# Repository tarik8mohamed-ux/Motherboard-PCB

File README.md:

# Hyperloop Motherboard PCB
Hyperloop Motherboard PCB Design (KiCad Schematics, component footprints, layouts, and diagrams)

Cornell Hyperloop SP'26
ECC:   Tarik, Peri, Farah, and Vinny

## Introduction: 
This project is a central control PCB designed to serve as the primary communication and motor control hub for Cornell Hyperloop's MiniPod. The board integrates multiple communication protocols to interface with a variety of peripherals: CANopen for servo motor control via the EPOS2 70/10, Step/Dir for stepper motor control via the TB6600, I2C for a distributed sensor network of temperature and current monitors, and PWM for fan speed control. The modular architecture supports hot-pluggable expansion, allowing sensors, MCU, and Multiplexers to be swapped or added without disrupting system operation. The board is ~265mm x 135mm and consists of 4 Layers: Signal-GND-PWR-Signal, with the PWR plane seperated into 3.3V,5.0V, and 12V sections to support different components. The most up to date files are in the Hyperloop Organized PCB folder.

## Components:
Cornell Hyperloop's MiniPod is ~7ft, meaning that sesnors and motors must be controlled by the motherbaord from a distance. This is why most components will be connected to the PCB via Cable/Wire connectors.
#### MCU:
The motherboard is controlled with an Arduino Nano R4
<table>
  <tr>
    <td align="center"><b>Arduino Nano R4</b></td>
  </tr>
  <tr>
    <td></td>
  </tr>
</table>

#### Sensors & Fan Control:
Overheating and current spikes are critical concerns on the Pod, so temperature and current sensors are distributed throughout. Temperature sensors use 8-pin Molex connectors (2 power, 2 communication, 1 interrupt, 3 alert pins), while current sensors use 4-pin Molex connectors (2 power, 2 communication pins). Vin+ and Vin− are connected across the points being measured, not the board, and I²C addresses are permanently hardset on the board. Additionally, a TCA9548A I2C multiplexer was integrated to expand the single I2C bus into up to 8 independent channels. 4-pin cooling fans are also distributed across the Pod, represented as 4-pin Molex connectors.
<table>
  <tr>
    <td align="center"><b>Temperature Sensor: MCP9808 </b></td>
    <td align="center"><b>Current Sensor: INA260</b></td>
    <td align="center"><b>Fan: Arctic P12</b></td>
    <td align="center"><b>Multiplexer: TCA9548A</b></td>
  </tr>
  <tr>
    <td></td>
    <td></td>
    <td></td>
    <td></td>
  </tr>
</table>

#### Motor Control:
The Pod interfaces with a TB6600 stepper driver and an EPOS2 70/10 servo controller. The TB6600 is controlled via Step/Dir/Enable signals through a Phoenix Contact screw terminal, and the EPOS2 communicates over CANopen through a Molex Micro-Fit 3.0 4-pin connector.
<table>
  <tr>
    <td align="center"><b>4-pin Pheonix Contact Screw Terminal</b></td>
    <td align="center"><b>Molex Micro-Fir 3.0 4-pin connector</b></td>
  </tr>
  <tr>
    <td></td>
    <td></td>
  </tr>
</table>

#### GPIO Expander:
An MCP23017 I2C expander is included to provide additional GPIO pins for the Pod as needed. Breakout headers expose all 16 I/O pins for flexible peripheral connections.
The motherboard is controlled with an Arduino Nano R4
<table>
  <tr>
    <td align="center"><b>MCP23017 I2C Expander:</b></td>
  </tr>
  <tr>
    <td></td>
  </tr>
</table>

#### Power, Resistors, Capacitors:
The PCB contains 3.3V,5.0V, and 12.0V sections in the power plane. XT30 connectors will be used to connect external battery packs to drive the power plane.
Resistors typically take on the role of pull-ups in this design. Through-Hole Resistors are used for ease of soldering. On the other hand, capacitors are typically used for bypass or decoupling. In this context, we picked SMD capacitors despite the extra difficulty in soldering because they significantly outperform THT.
<table>
  <tr>
    <td align="center"><b>XT30 Connector:</b></td>
  </tr>
  <tr>
    <td></td>
  </tr>
</table>

## Communication Systems:
### I2C Sensor Network & I2C Expander:
The I2C network, located in the top left of the PCB, is managed by a TCA9548A multiplexer which expands the microcontroller's single I2C bus into 4 independent channels, each with its own pull-up resistors to maintain signal integrity. Each channel hosts sensor peripherals, with every device supported by a dedicated decoupling capacitor for noise suppression. A series resistor on the main I2C line dampens inductive ringing before the signal reaches the multiplexer. MCP9808 temperature sensors feature an active-low alert pin connected to a microcontroller GPIO, enabling interrupt-driven temperature monitoring without continuous polling. An MCP23017 I2C I/O expander is also connected to the bus, currently populated with breakout headers for flexible future peripheral connections.

### CAN EPOS2 70/10:
CANopen communication is implemented using a TCAN332 transceiver, which converts the microcontroller's TX/RX signals into differential CANH/CANL signals. A 120Ω termination resistor is placed at the output connector to prevent signal reflections. The bus connects to an EPOS2 70/10 servo controller via a Molex Micro-Fit 3.0 cable. It is located below the MCU.

### Step/Dir TB6600:
The TB6600 stepper driver is controlled via three GPIO signals — PUL+, DIR+, and ENA+ — using a common-cathode wiring configuration. Series resistors on each line dampen signal ringing before reaching the Phoenix Contact screw terminal output connector. It is located just above the MCU.

### PWM Fan CTRL:
Two pairs of fans are controlled via PWM signals from the microcontroller, with each pair sharing a single PWM output to conserve GPIO pins. One tachometer signal per pair is routed back to a microcontroller GPIO, providing RPM feedback for monitoring fan speed. Each fan connector includes dedicated power and ground connections for reliable operation. It is located on the right side of the board.

## Future Updates
-INA260 Alert Pin: The INA260 current sensor connector will be expanded from 4 to 5 pins to expose the ALERT pin, enabling interrupt-driven current monitoring in place of polling across the I2C channels and significantly improving CPU efficiency.    

-TCAN332 Connector Orientation: The CAN connector will be changed from horizontal to vertical to improve accessibility and PCB layout clarity.

-Component Density: Component placement will be optimized for a smaller board footprint, reducing fabrication cost.

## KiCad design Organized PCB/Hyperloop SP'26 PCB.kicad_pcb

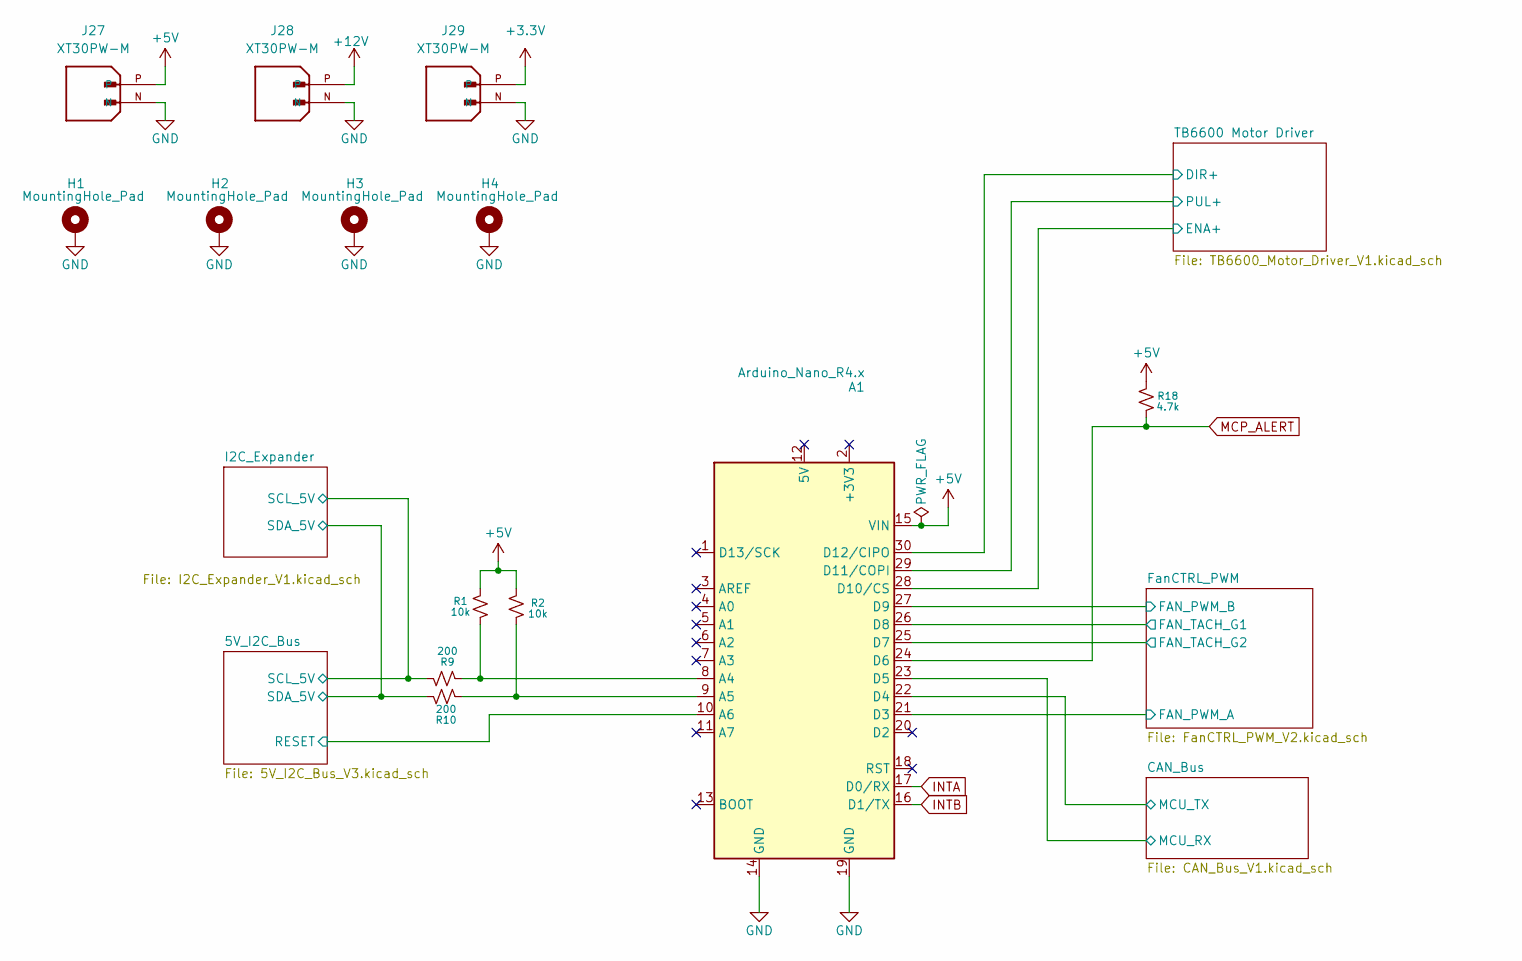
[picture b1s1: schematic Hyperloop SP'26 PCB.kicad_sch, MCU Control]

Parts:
A1: Arduino_Nano_R4.x; Arduino_Nano
H1, H2, H3, H4: MountingHole_Pad; MountingHole_3.2mm_M3_Pad_TopBottom
J27, J28, J29: XT30PW-M; AMASS_XT30PW-M; PARTREV 1.2
R1, R2: 10k; R_Axial_DIN0207_L6.3mm_D2.5mm_P7.62mm_Horizontal
R9, R10: 200; R_Axial_DIN0207_L6.3mm_D2.5mm_P7.62mm_Horizontal
R18: 4.7k; R_Axial_DIN0207_L6.3mm_D2.5mm_P7.62mm_Horizontal

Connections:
+3.3V: J29.P; also elsewhere on the board
+5V: A1.15 (VIN), J27.P, R1.2, R2.2, R18.2; also elsewhere on the board
+12V: J28.P; also elsewhere on the board
/5V_I2C_Bus/RESET: A1.10 (A6); also elsewhere on the board
/5V_I2C_Bus/SCL_5V: R9.2; also elsewhere on the board
/5V_I2C_Bus/SDA_5V: R10.2; also elsewhere on the board
/CAN_Bus/MCU_RX: A1.23 (D5); also elsewhere on the board
/CAN_Bus/MCU_TX: A1.22 (D4); also elsewhere on the board
/FanCTRL_PWM/FAN_PWM_A: A1.21 (D3); also elsewhere on the board
/FanCTRL_PWM/FAN_PWM_B: A1.27 (D9); also elsewhere on the board
/FanCTRL_PWM/FAN_TACH_G1: A1.26 (D8); also elsewhere on the board
/FanCTRL_PWM/FAN_TACH_G2: A1.25 (D7); also elsewhere on the board
/TB6600 Motor Driver/DIR+: A1.30 (D12/CIPO); also elsewhere on the board
/TB6600 Motor Driver/ENA+: A1.28 (D10/CS); also elsewhere on the board
/TB6600 Motor Driver/PUL+: A1.29 (D11/COPI); also elsewhere on the board
GND: A1.14 (GND), A1.19 (GND), H1.1, H2.1, H3.1, H4.1, J27.N, J28.N, J29.N; also elsewhere on the board
INTA: A1.17 (D0/RX); also elsewhere on the board
INTB: A1.16 (D1/TX); also elsewhere on the board
MCP_ALERT: A1.24 (D6), R18.1; also elsewhere on the board
unnamed: A1.8 (A4), R1.1, R9.1
unnamed: A1.9 (A5), R2.1, R10.1

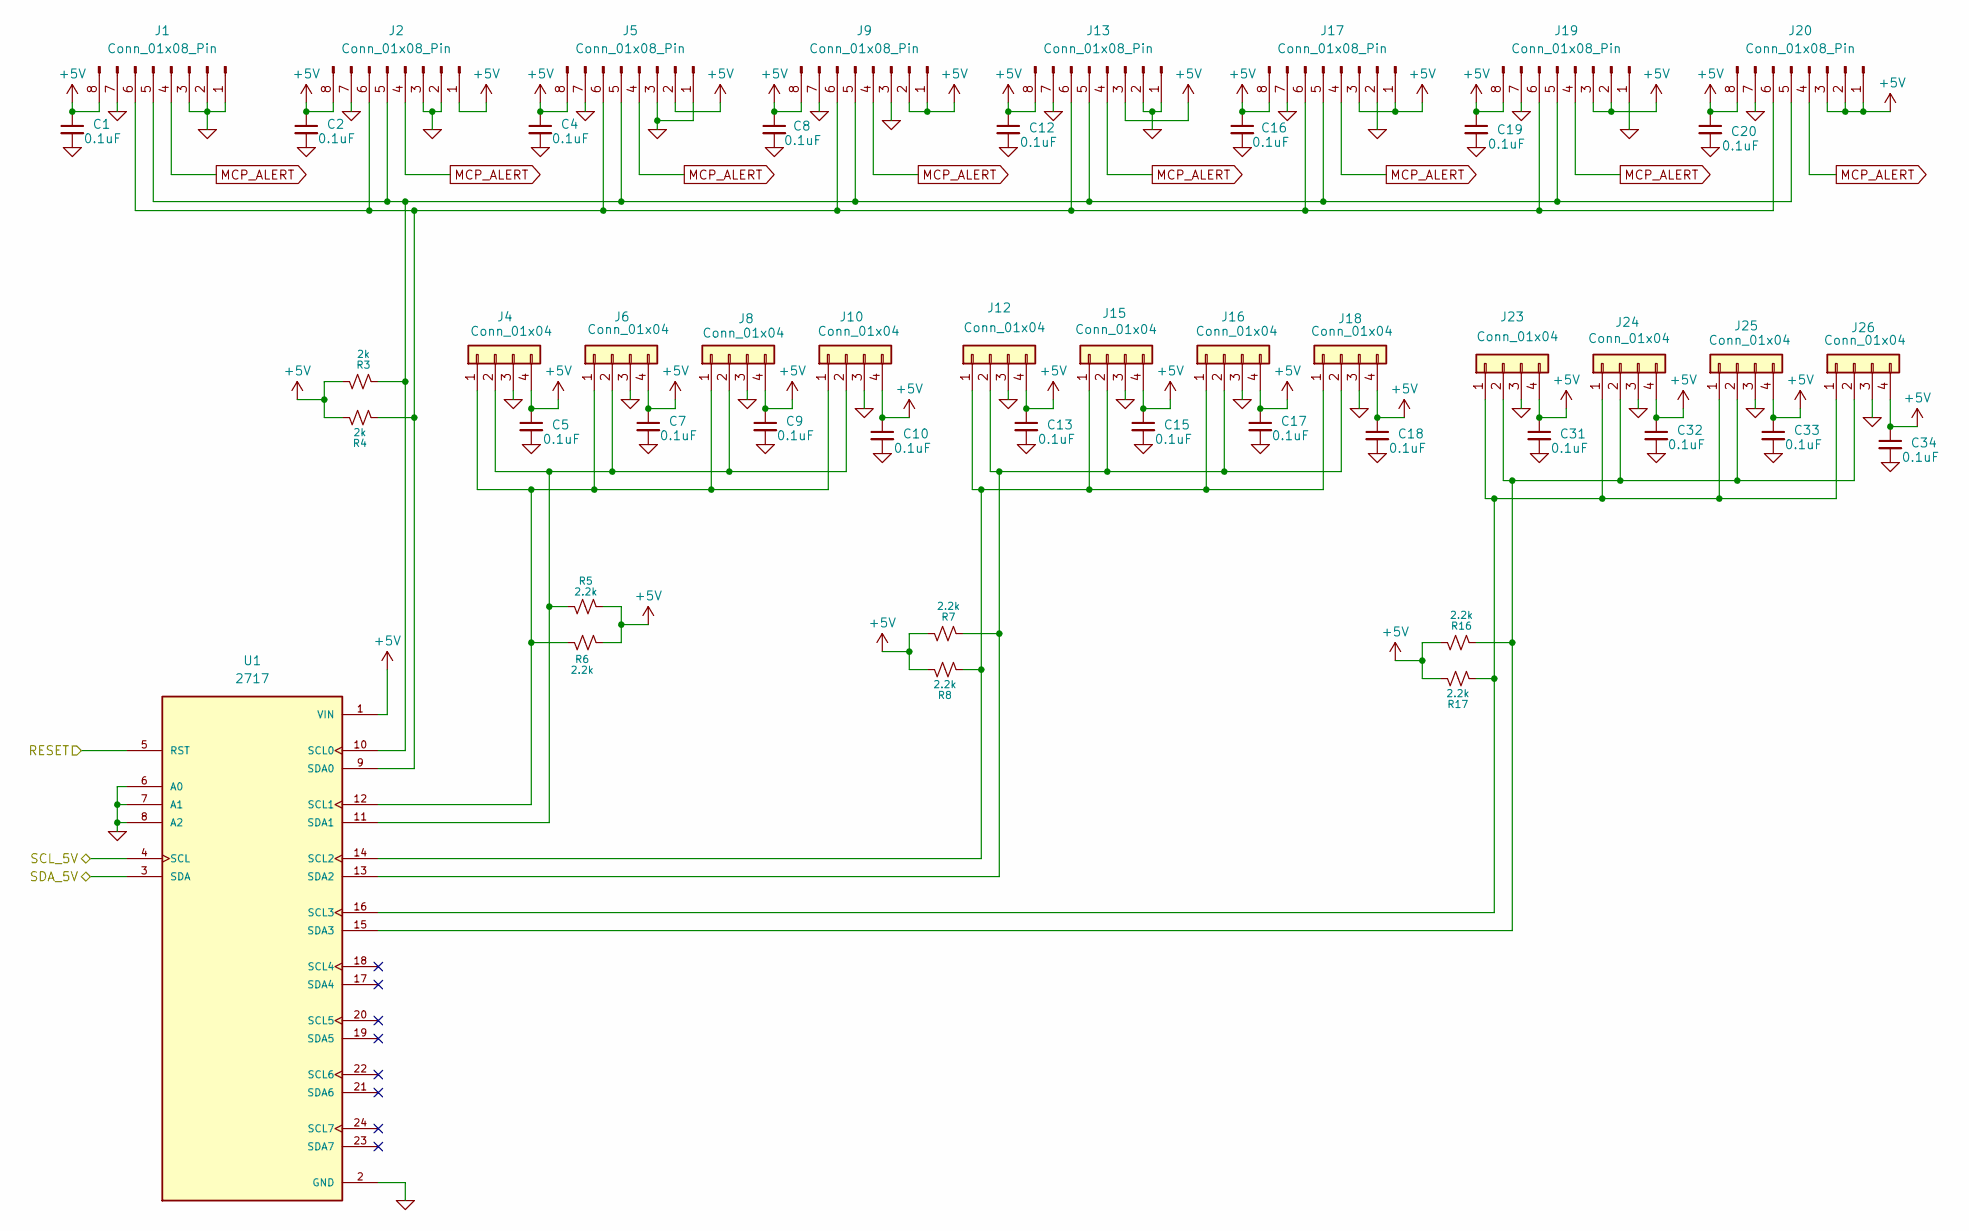
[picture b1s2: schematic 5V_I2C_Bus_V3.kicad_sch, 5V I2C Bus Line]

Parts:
C1, C2, C4, C5, C7, C8, C9, C10, C12, C13, C15, C16, C17, C18, C19, C20, C31, C32, C33, C34: 0.1uF; C_0805_2012Metric
J1, J2, J5, J9, J13, J17, J19, J20: Conn_01x08_Pin; Molex_KK-254_AE-6410-08A_1x08_P2.54mm_Vertical
J4, J6, J8, J10, J12, J15, J16, J18, J23, J24, J25, J26: Conn_01x04; Molex_KK-254_AE-6410-04A_1x04_P2.54mm_Vertical
R3, R4: 2k; R_Axial_DIN0207_L6.3mm_D2.5mm_P7.62mm_Horizontal
R5, R6, R7, R8, R16, R17: 2.2k; R_Axial_DIN0207_L6.3mm_D2.5mm_P7.62mm_Horizontal
U1: 2717; MODULE_2717; PARTREV Sep 11, 2015

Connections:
+5V: C1.1, C2.1, C4.1, C5.1, C7.1, C8.1, C9.1, C10.1, C12.1, C13.1, C15.1, C16.1, C17.1, C18.1, C19.1, C20.1, C31.1, C32.1, C33.1, C34.1, J1.8, J2.1, J2.8, J4.4, J5.2, J5.8, J6.4, J8.4, J9.1, J9.2, J9.8, J10.4, J12.4, J13.3, J13.8, J15.4, J16.4, J17.1, J17.3, J17.8, J18.4, J19.2, J19.3, J19.8, J20.1, J20.2, J20.3, J20.8, J23.4, J24.4, J25.4, J26.4, R3.2, R4.2, R5.2, R6.2, R7.2, R8.2, R16.2, R17.2, U1.1 (VIN); also elsewhere on the board
/5V_I2C_Bus/RESET: U1.5 (RST); also elsewhere on the board
/5V_I2C_Bus/SCL_5V: U1.4 (SCL); also elsewhere on the board
/5V_I2C_Bus/SDA_5V: U1.3 (SDA); also elsewhere on the board
GND: C1.2, C2.2, C4.2, C5.2, C7.2, C8.2, C9.2, C10.2, C12.2, C13.2, C15.2, C16.2, C17.2, C18.2, C19.2, C20.2, C31.2, C32.2, C33.2, C34.2, J1.1, J1.2, J1.3, J1.7, J2.2, J2.3, J2.7, J4.3, J5.1, J5.3, J5.7, J6.3, J8.3, J9.3, J9.7, J10.3, J12.3, J13.1, J13.2, J13.7, J15.3, J16.3, J17.2, J17.7, J18.3, J19.1, J19.7, J20.7, J23.3, J24.3, J25.3, J26.3, U1.2 (GND), U1.6 (A0), U1.7 (A1), U1.8 (A2); also elsewhere on the board
MCP_ALERT: J1.4, J2.4, J5.4, J9.4, J13.4, J17.4, J19.4, J20.4; also elsewhere on the board
unnamed: J1.5, J2.5, J5.5, J9.5, J13.5, J17.5, J19.5, J20.5, R3.1, U1.10 (SCL0)
unnamed: J1.6, J2.6, J5.6, J9.6, J13.6, J17.6, J19.6, J20.6, R4.1, U1.9 (SDA0)
unnamed: J4.1, J6.1, J8.1, J10.1, R6.1, U1.12 (SCL1)
unnamed: J4.2, J6.2, J8.2, J10.2, R5.1, U1.11 (SDA1)
unnamed: J12.1, J15.1, J16.1, J18.1, R8.1, U1.14 (SCL2)
unnamed: J12.2, J15.2, J16.2, J18.2, R7.1, U1.13 (SDA2)
unnamed: J23.1, J24.1, J25.1, J26.1, R17.1, U1.16 (SCL3)
unnamed: J23.2, J24.2, J25.2, J26.2, R16.1, U1.15 (SDA3)

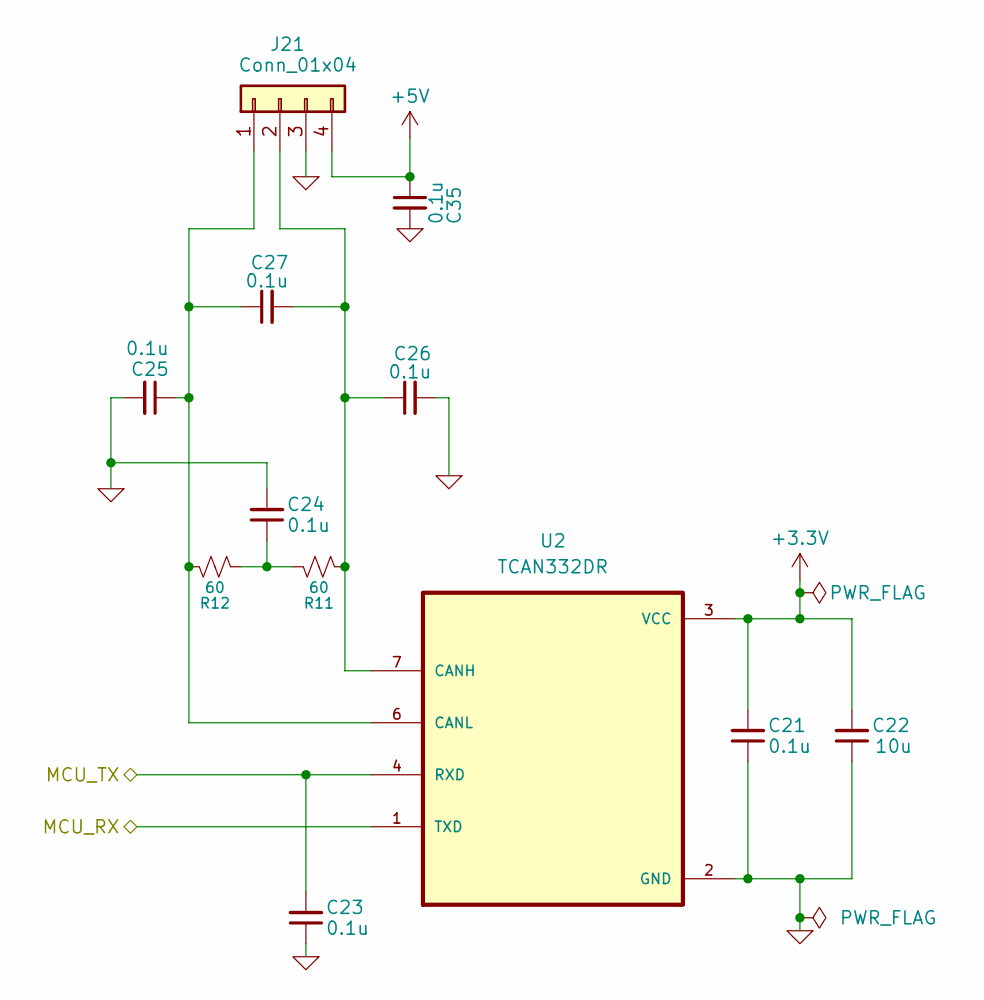
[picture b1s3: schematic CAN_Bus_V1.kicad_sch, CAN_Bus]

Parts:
C21, C23, C24, C25, C26, C27, C35: 0.1u; C_0805_2012Metric
C22: 10u; C_0805_2012Metric
J21: Conn_01x04; Molex_Micro-Fit_3.0_43045-0400_2x02_P3.00mm_Horizontal
R11, R12: 60; R_Axial_DIN0207_L6.3mm_D2.5mm_P7.62mm_Horizontal
U2: TCAN332DR; SOIC127P599X175-8N(TCAN332DR)

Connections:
+3.3V: C21.2, C22.2, U2.3 (VCC); also elsewhere on the board
+5V: C35.1, J21.4; also elsewhere on the board
/CAN_Bus/MCU_RX: U2.1 (TXD); also elsewhere on the board
/CAN_Bus/MCU_TX: C23.2, U2.4 (RXD); also elsewhere on the board
GND: C21.1, C22.1, C23.1, C24.2, C25.2, C26.2, C35.2, J21.3, U2.2 (GND); also elsewhere on the board
unnamed: C24.1, R11.2, R12.1
unnamed: C25.1, C27.1, J21.1, R12.2, U2.6 (CANL)
unnamed: C26.1, C27.2, J21.2, R11.1, U2.7 (CANH)

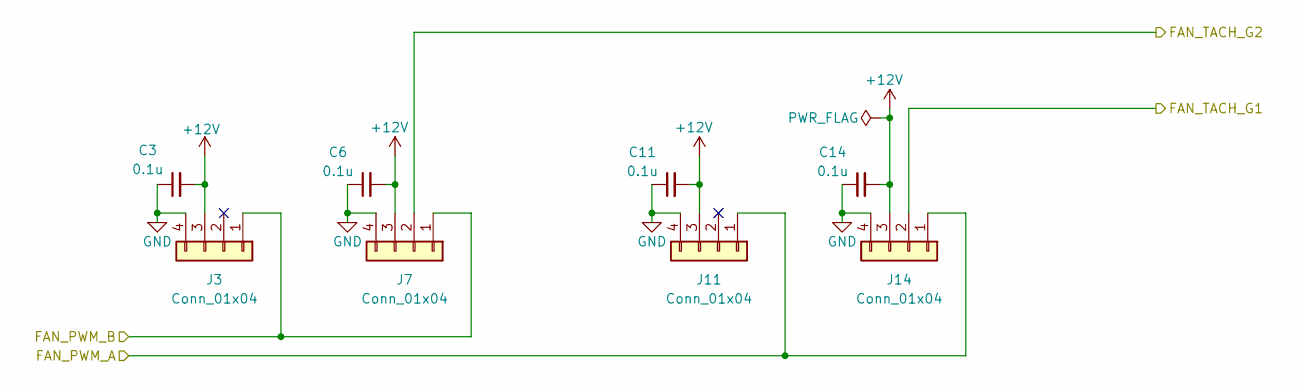
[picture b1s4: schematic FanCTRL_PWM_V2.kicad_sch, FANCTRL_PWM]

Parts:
C3, C6, C11, C14: 0.1u; C_0805_2012Metric
J3, J7, J11, J14: Conn_01x04; Molex_KK-254_AE-6410-04A_1x04_P2.54mm_Vertical

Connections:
+12V: C3.2, C6.2, C11.2, C14.2, J3.3, J7.3, J11.3, J14.3; also elsewhere on the board
/FanCTRL_PWM/FAN_PWM_A: J11.1, J14.1; also elsewhere on the board
/FanCTRL_PWM/FAN_PWM_B: J3.1, J7.1; also elsewhere on the board
/FanCTRL_PWM/FAN_TACH_G1: J14.2; also elsewhere on the board
/FanCTRL_PWM/FAN_TACH_G2: J7.2; also elsewhere on the board
GND: C3.1, C6.1, C11.1, C14.1, J3.4, J7.4, J11.4, J14.4; also elsewhere on the board

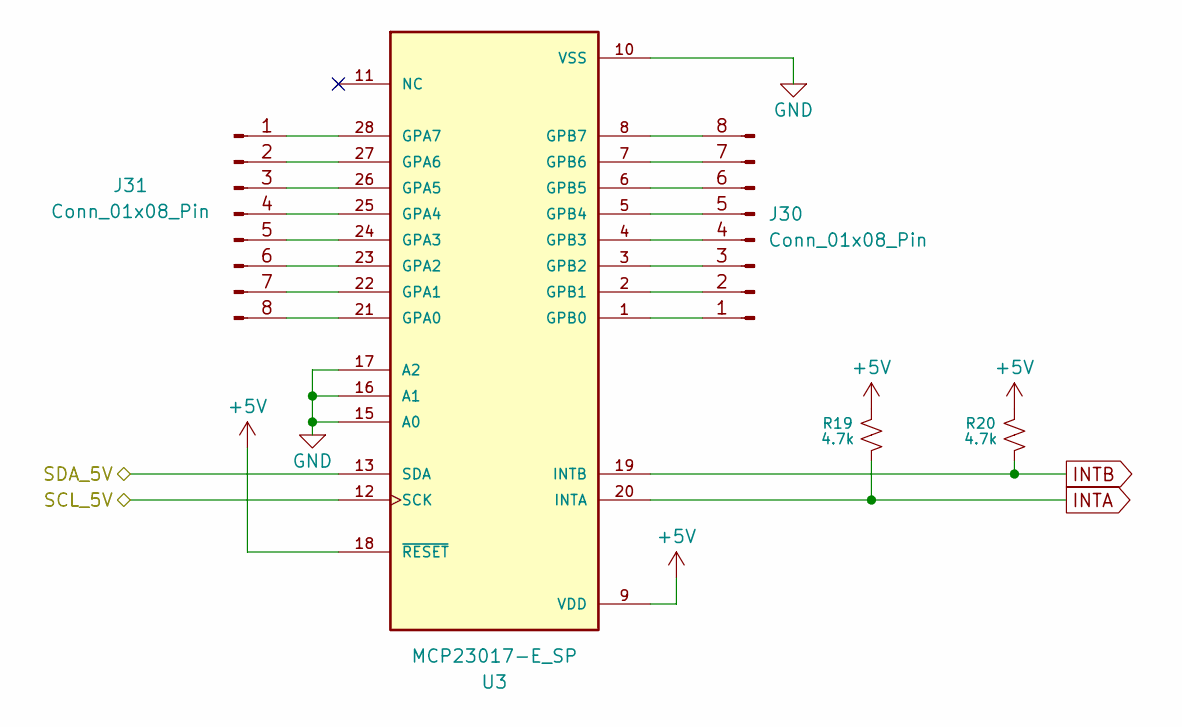
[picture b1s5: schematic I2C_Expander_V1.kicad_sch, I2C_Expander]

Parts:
J30, J31: Conn_01x08_Pin; PinHeader_1x08_P2.54mm_Vertical
R19, R20: 4.7k; R_Axial_DIN0207_L6.3mm_D2.5mm_P7.62mm_Horizontal
U3: MCP23017-E_SP; MCP23017(IO Expander); PARTREV D

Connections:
+5V: R19.1, R20.1, U3.9 (VDD), U3.18 (~RESET); also elsewhere on the board
/5V_I2C_Bus/SCL_5V: U3.12 (SCK); also elsewhere on the board
/5V_I2C_Bus/SDA_5V: U3.13 (SDA); also elsewhere on the board
GND: U3.10 (VSS), U3.15 (A0), U3.16 (A1), U3.17 (A2); also elsewhere on the board
INTA: R19.2, U3.20 (INTA); also elsewhere on the board
INTB: R20.2, U3.19 (INTB); also elsewhere on the board
unnamed: J30.1, U3.1 (GPB0)
unnamed: J30.2, U3.2 (GPB1)
unnamed: J30.3, U3.3 (GPB2)
unnamed: J30.4, U3.4 (GPB3)
unnamed: J30.5, U3.5 (GPB4)
unnamed: J30.6, U3.6 (GPB5)
unnamed: J30.7, U3.7 (GPB6)
unnamed: J30.8, U3.8 (GPB7)
unnamed: J31.1, U3.28 (GPA7)
unnamed: J31.2, U3.27 (GPA6)
unnamed: J31.3, U3.26 (GPA5)
unnamed: J31.4, U3.25 (GPA4)
unnamed: J31.5, U3.24 (GPA3)
unnamed: J31.6, U3.23 (GPA2)
unnamed: J31.7, U3.22 (GPA1)
unnamed: J31.8, U3.21 (GPA0)

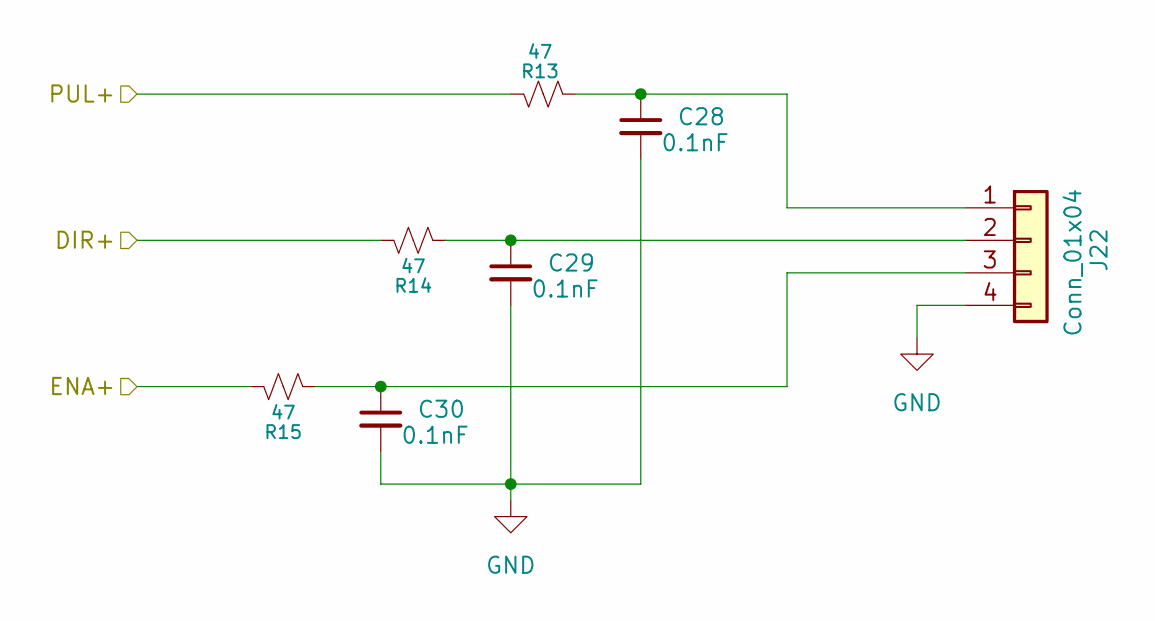
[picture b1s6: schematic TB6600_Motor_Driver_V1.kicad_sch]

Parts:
C28, C29, C30: 0.1nF; C_0805_2012Metric
J22: Conn_01x04; TerminalBlock_Phoenix_PT-1,5-4-3.5-H_1x04_P3.50mm_Horizontal
R13, R14, R15: 47; R_Axial_DIN0207_L6.3mm_D2.5mm_P7.62mm_Horizontal

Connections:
/TB6600 Motor Driver/DIR+: R14.2; also elsewhere on the board
/TB6600 Motor Driver/ENA+: R15.2; also elsewhere on the board
/TB6600 Motor Driver/PUL+: R13.2; also elsewhere on the board
GND: C28.2, C29.2, C30.2, J22.4; also elsewhere on the board
unnamed: C28.1, J22.1, R13.1
unnamed: C29.1, J22.2, R14.1
unnamed: C30.1, J22.3, R15.1

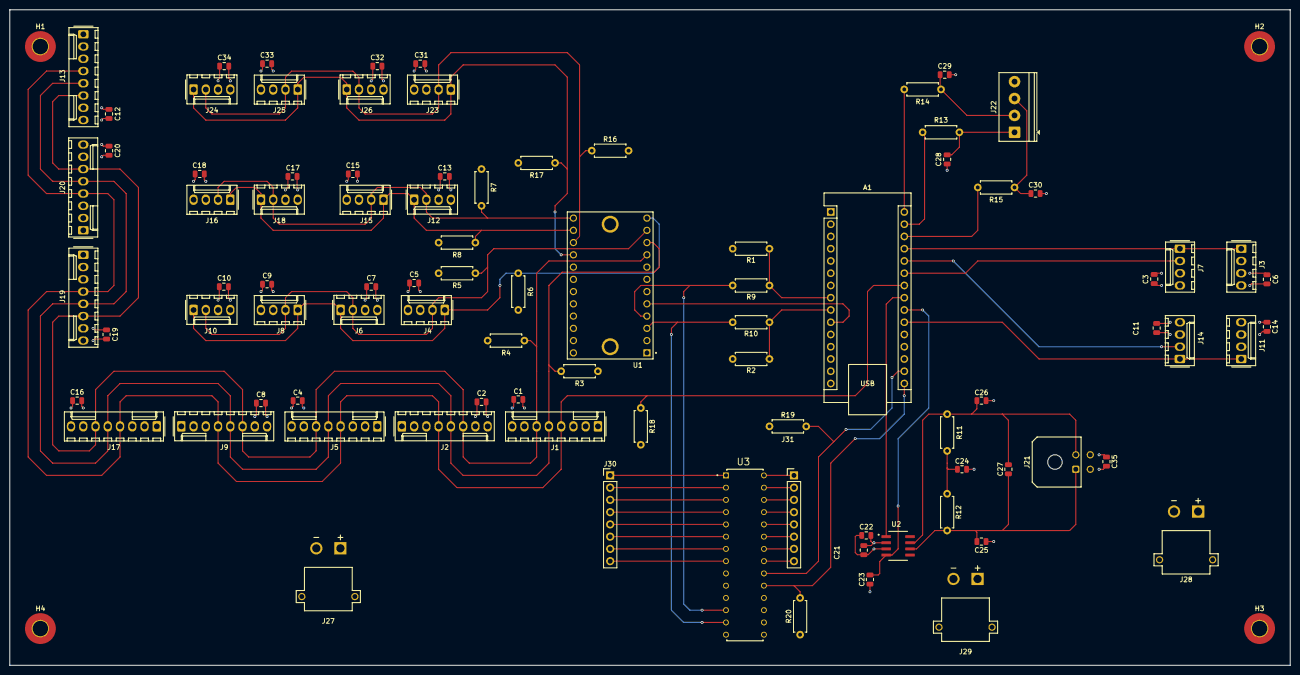
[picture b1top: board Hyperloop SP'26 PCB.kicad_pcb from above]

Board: 4 copper layers, 265.4 x 135.9 mm, 94 parts (0 on the bottom side), 51 nets.

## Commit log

2026-05-19 Upload
2026-05-19 Revise README with updated images and sensor info
    Updated images and sensor descriptions in the README to reflect changes in components and connections.
